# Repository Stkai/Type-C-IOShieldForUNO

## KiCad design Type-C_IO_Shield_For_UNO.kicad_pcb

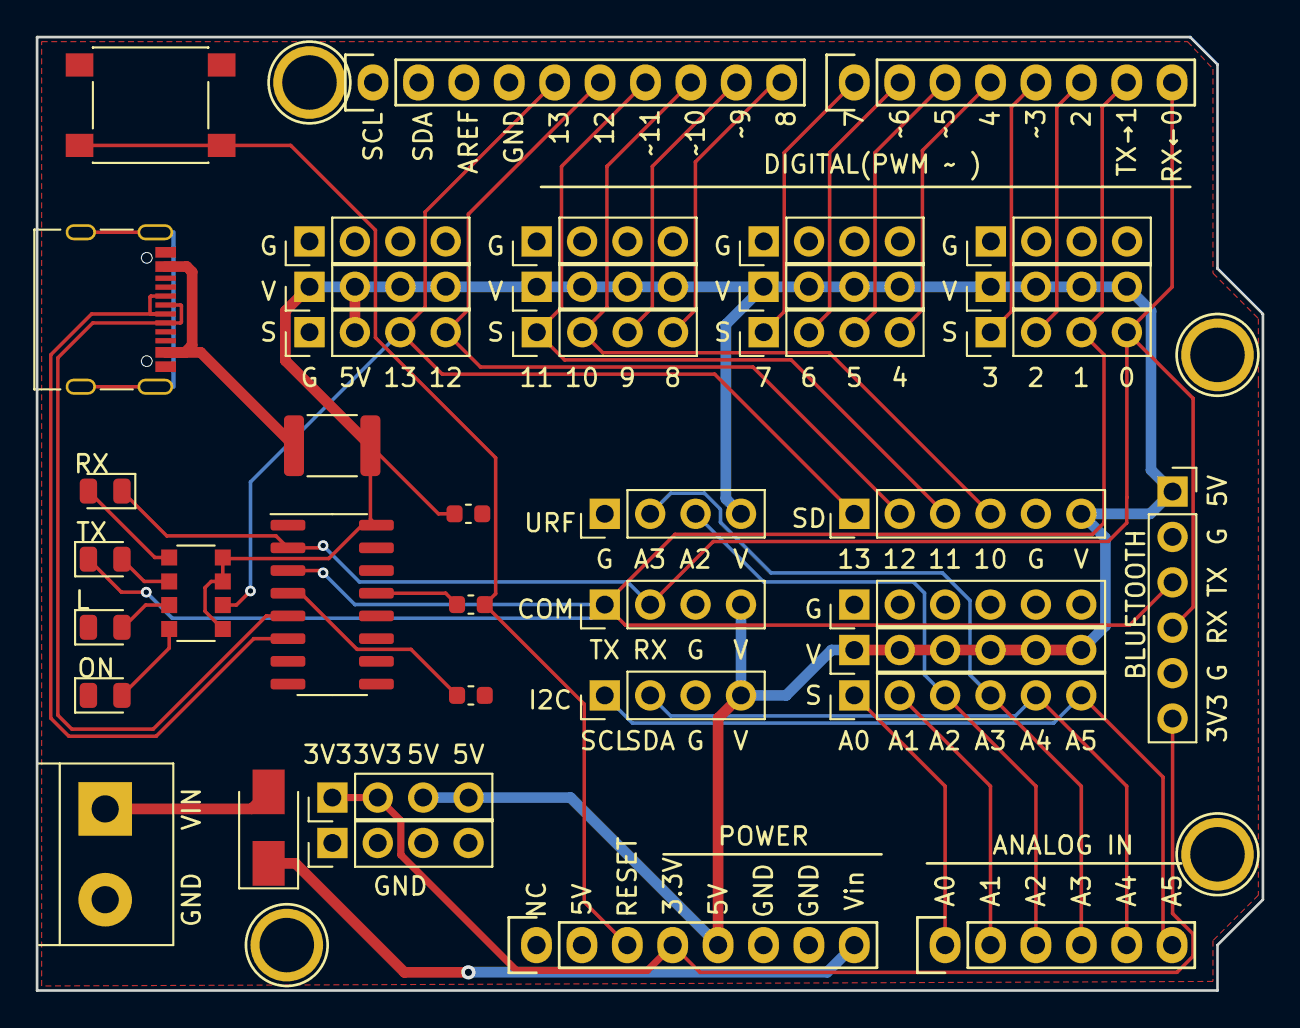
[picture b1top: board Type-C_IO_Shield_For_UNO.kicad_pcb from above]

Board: 2 copper layers, 68.6 x 53.3 mm, 44 parts (0 on the bottom side), 35 nets.

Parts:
C1, C2: 104; C_0603_1608Metric
C3: 105; C_0603_1608Metric
D1: GREEN; LED_0805_2012Metric
D2, D3, D4: YELLOW; LED_0805_2012Metric
D5: 1N4007; D_SMA
F1: 0.5A; Fuse_1812_4532Metric
J1, J2, J3, J5, J6, J7, J10, J11, J12, J13, J14, J15, J21, J22, J23, J24, J25: Conn_01x04; PinHeader_1x04_P2.54mm_Vertical
J4: USB_C_Receptacle_USB2.0; USB_C_Receptacle_Palconn_UTC16-G
J17, J18, J19, J26: Conn_01x06; PinHeader_1x06_P2.54mm_Vertical
J27: Conn_01x06; PinSocket_1x06_P2.54mm_Vertical
J28: Screw_Terminal_01x02; TerminalBlock_bornier-2_P5.08mm
P1: Power; Socket_Strip_Arduino_1x08
P2: Analog; Socket_Strip_Arduino_1x06
P3: Digital; Socket_Strip_Arduino_1x10
P4: Digital; Socket_Strip_Arduino_1x08
P5, P6, P7, P8: CONN_01X01; Arduino_1pin
RN1: 102; R_Array_Convex_4x1206
SW1: SW_SPST; SW_Push_1P1T_NO_6x6mm_H9.5mm
U1: CH340C; SOIC-16_3.9x9.9mm_P1.27mm

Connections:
+3V3: J21.1, J21.2, J27.6, P1.4
+5V: C2.1, F1.2, J2.1, J2.2, J2.3, J2.4, J3.2, J6.1, J6.2, J6.3, J6.4, J11.1, J11.2, J11.3, J11.4, J14.1, J14.2, J14.3, J14.4, J18.1, J18.2, J18.3, J18.4, J18.5, J18.6, J21.3, J21.4, J23.4, J24.4, J25.4, J26.6, J27.1, P1.5, RN1.1 (R1.1), RN1.3 (R3.1), RN1.4 (R4.1), U1.16 (VCC)
/0(Rx): D4.1 (K), J15.4, J24.2, J27.4, P4.8, U1.2 (TXD)
/1(Tx): D3.1 (K), J15.3, J24.1, J27.3, P4.7, U1.3 (RXD)
/2: J15.2, P4.6
/3(**): J15.1, P4.5
/4: J12.4, P4.4
/5(**): J12.3, P4.3
/6(**): J12.2, P4.2
/7: J12.1, P4.1
/8: J7.4, P3.10
/9(**): J7.3, P3.9
/10(**/SS): J7.2, J26.4, P3.8
/11(**/MOSI): J7.1, J26.3, P3.7
/12(MISO): J3.4, J26.2, P3.6
/13(SCK): J3.3, J26.1, P3.5, RN1.2 (R2.1)
/A0: J19.1, P2.1
/A1: J19.2, P2.2
/A2: J19.3, J25.3, P2.3
/A3: J19.4, J25.2, P2.4
/A4(SDA): J19.5, J23.2, P2.5, P3.2
/A5(SCL): J19.6, J23.1, P2.6, P3.1
/Reset: C3.1, P1.3, SW1.2 (B)
/Vin: D5.1 (K), P1.8
GND: C1.1, C2.2, D1.1 (K), D2.1 (K), J1.1, J1.2, J1.3, J1.4, J3.1, J4.A1 (GND), J4.A12 (GND), J4.B1 (GND), J4.B12 (GND), J5.1, J5.2, J5.3, J5.4, J10.1, J10.2, J10.3, J10.4, J13.1, J13.2, J13.3, J13.4, J17.1, J17.2, J17.3, J17.4, J17.5, J17.6, J22.1, J22.2, J22.3, J22.4, J23.3, J24.3, J25.1, J26.5, J27.2, J27.5, J28.2, P1.6, P1.7, P3.4, SW1.1 (A), U1.1 (GND)
unnamed: C1.2, U1.4 (V3)
unnamed: C3.2, U1.13 (~DTR)
unnamed: D1.2 (A), RN1.8 (R1.2)
unnamed: D2.2 (A), RN1.7 (R2.2)
unnamed: D3.2 (A), RN1.6 (R3.2)
unnamed: D4.2 (A), RN1.5 (R4.2)
unnamed: D5.2 (A), J28.1
unnamed: F1.1, J4.A4 (VBUS), J4.A9 (VBUS), J4.B4 (VBUS), J4.B9 (VBUS)
unnamed: J4.A6 (D+), J4.B6 (D+), U1.5 (UD+)
unnamed: J4.A7 (D-), J4.B7 (D-), U1.6 (UD-)

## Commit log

2022-02-27 Type-C IO Shield For UNO
2022-02-28 update sch
2022-03-01 V1.1
2022-03-02 update pcb
2022-03-02 V1.2
2022-03-03 typo
2022-03-03 update usb location

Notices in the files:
Type-C_IO_Shield_For_UNO.kicad_pcb:
Copyright © 2022 St.kai.
Available under the GNU General Public License v3.0 or later.
